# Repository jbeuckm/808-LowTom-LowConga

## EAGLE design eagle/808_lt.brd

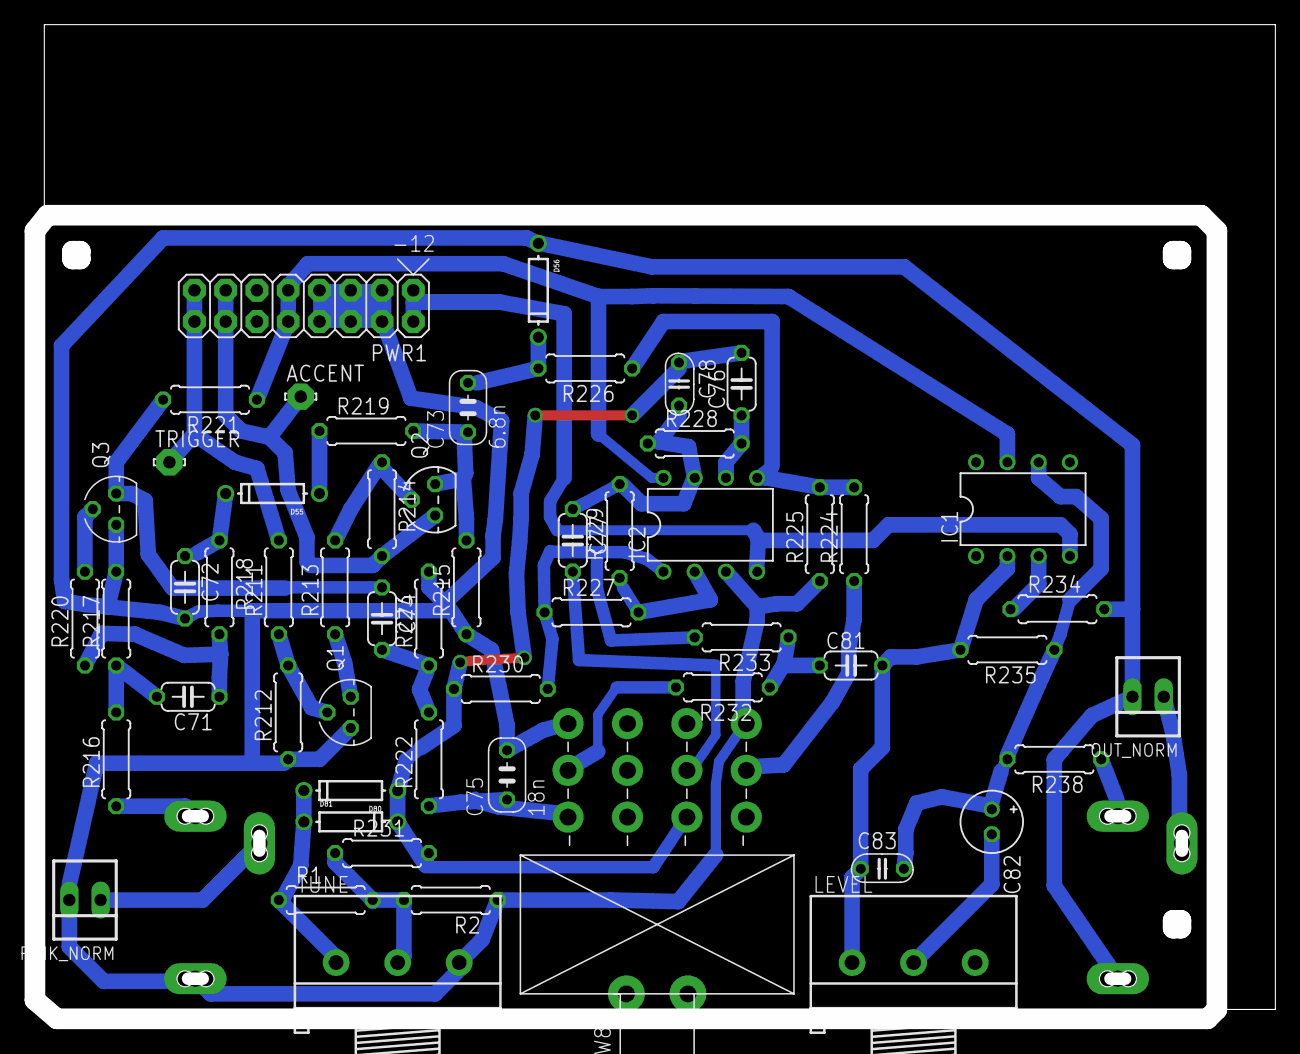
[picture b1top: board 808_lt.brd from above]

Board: 2 copper layers, 100.8 x 80.8 mm, 58 parts (0 on the bottom side), 38 nets.

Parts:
ACCENT: LSP10
C71, C74, C77, C81: 47n; C050-024X044
C72: 39n; C050-024X044
C73: 6.8n; C035-030X60
C75: 18n; C035-030X60
C76: 56n; C050-024X044
C78: 12n; C035-025X75
C82: 33/6.3; E2-5
C83: 1n; C035-025X75
D55, D56, D80, D81: DO-1N4148
IC1: TL071P; DIL08
IC2: TL072P; DIL08
LEVEL: 100k; 3RP/1610N
OUTPUT: AUDIO-JACK; ERTHENVAR-JACK-90DEG
OUT_NORM: 22-23-2021
PINK_NOISE: AUDIO-JACK; ERTHENVAR-JACK-90DEG
PINK_NORM: 22-23-2021
PWR1: POWER; POWER_16
Q1, Q3: 2N3904; TO92
Q2: 2N3906; TO92
R1, R2: 263R; 0207/7
R211, R222, R223, R226: 22K; 0207/7
R212, R213: 10K; 0207/7
R214, R215, R219, R221, R225: 4K7; 0207/7
R216: 15K; 0207/7
R217: 3K3; 0207/7
R218: 2M2; 0207/7
R220, R227, R229: 33K; 0207/7
R224: 1K5; 0207/7
R228, R230: 820K; 0207/7
R231, R238: 1K; 0207/7
R232, R233: 100K; 0207/7
R234: 47K; 0207/7
R235: 470K; 0207/7
SW8: 808_LT_MSS42_SW_4PDT; 808_LT_MSS42_SW_SLIDE
TRIGGER: LSP10
TUNE: 10k; 3RP/1610N

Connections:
+15V: IC1.7, IC2.8, PWR1.9, PWR1.10, R221.1
-15V: IC1.4, IC2.4, PWR1.1, PWR1.2
GND: C72.2, C75.P$2, D56.A, IC2.3, OUTPUT.P$1, OUT_NORM.2, PINK_NOISE.P$1, PINK_NORM.2, PWR1.3, PWR1.4, PWR1.5, PWR1.6, PWR1.7, PWR1.8, Q1.3, Q3.3, R2.1, R212.1, R215.1, R217.2, R223.2, R225.1, R234.2, SW8.P$3, SW8.P$12, TUNE.3
LT: PWR1.15, PWR1.16, R211.2, TRIGGER.MP
LT_LC_OUT: OUTPUT.P$3, R238.1
unnamed: Q3.2, R220.2
unnamed: Q1.1, R213.1
unnamed: OUTPUT.P$2, OUT_NORM.1
unnamed: PINK_NOISE.P$2, PINK_NORM.1
unnamed: IC2.5, R224.2, R225.2, R226.1
unnamed: IC1.3, R234.1
unnamed: R224.1, SW8.P$11
unnamed: Q2.2, R213.2, R214.1
unnamed: Q1.2, R211.1, R212.2
unnamed: C73.P$1, Q2.1, R215.2, R219.2
unnamed: D55.A, R219.1
unnamed: C73.P$2, D56.C, R226.2
unnamed: C76.2, C78.P$1, D80.A, D81.C, R230.1, R231.2, SW8.P$7
unnamed: C76.1, IC2.6, R228.2
unnamed: C77.1, C78.P$2, IC2.7, R228.1, R229.2
unnamed: D80.C, D81.A, R1.1, TUNE.1
unnamed: R1.2, R2.2, R231.1, TUNE.2
unnamed: IC2.2, R227.2, R229.1
unnamed: IC2.1, R227.1, R230.2, R233.2
unnamed: C81.1, R232.1, R233.1
unnamed: C81.2, C83.P$1, IC1.2, LEVEL.1, R235.2
unnamed: C82.-, LEVEL.2
unnamed: C82.+, C83.P$2, IC1.6, R235.1, R238.2
unnamed: C74.1, Q3.1, R221.2
unnamed: C75.P$1, R222.1, SW8.P$1
unnamed: C71.2, R216.2, R217.1
unnamed: C71.1, R218.2, R220.1
unnamed: C72.1, D55.C, R218.1
unnamed: C77.2, SW8.P$8
unnamed: R232.2, SW8.P$2
unnamed: C74.2, R222.2, R223.1
PN: PINK_NOISE.P$3, R216.1
TRIG: ACCENT.MP, PWR1.13, PWR1.14, Q2.3, R214.2

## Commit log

2016-04-15 initla commit
2016-04-15 board started
2016-04-15 routing in low 90s
2016-04-15 closer
2016-04-15 93 pct
2016-04-15 routed
2016-04-15 tweaks
2016-04-15 cutout
2016-04-16 thicker traces
2016-04-16 tweaked and gcode
2016-04-18 corrected 071 power and added resistors to tune pot for value change
2016-04-18 more thicker traces
2016-04-18 corrected 4pdt toggle body size
